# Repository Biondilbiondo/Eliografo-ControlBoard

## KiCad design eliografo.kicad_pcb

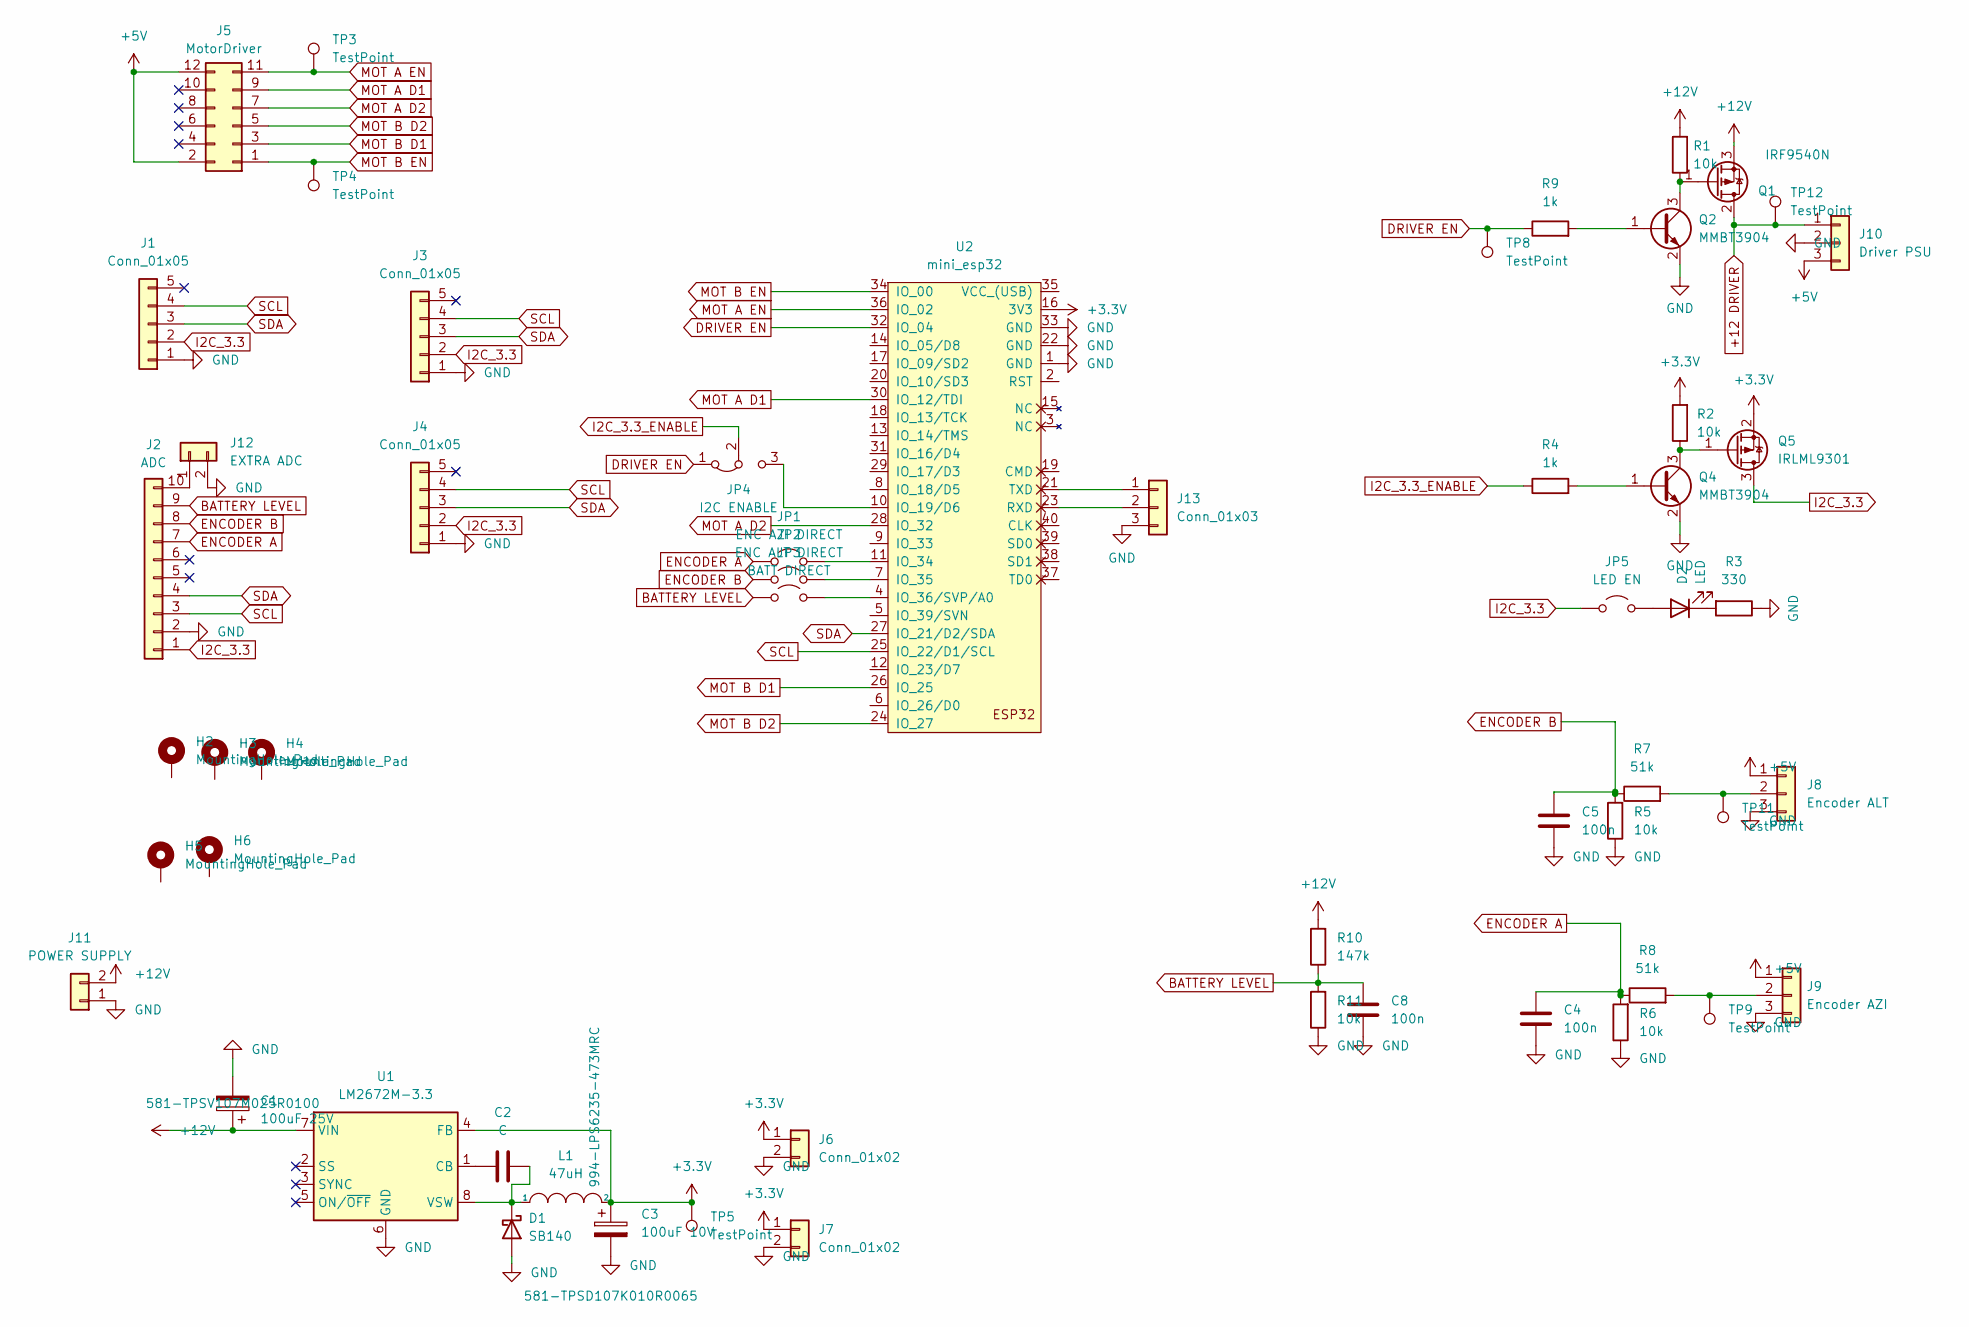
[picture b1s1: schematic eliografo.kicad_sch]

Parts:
C1: 100uF 25V; CP_EIA-7361-38_AVX-V_HandSolder
C2: C; C_0805_2012Metric_Pad1.18x1.45mm_HandSolder
C3: 100uF 10V; CP_EIA-7343-15_Kemet-W_HandSolder
C4, C5, C8: 100n; C_0805_2012Metric_Pad1.18x1.45mm_HandSolder
D1: SB140; D_SMA
D2: LED; LED_D3.0mm
H2, H3, H4, H5, H6: MountingHole_Pad; MountingHole_3.2mm_M3_Pad
J1, J3, J4: Conn_01x05; PinSocket_1x05_P2.54mm_Vertical
J2: ADC; PinSocket_1x10_P2.54mm_Vertical
J5: MotorDriver; IDC-Header_2x06_P2.54mm_Vertical
J6, J7: Conn_01x02; PinHeader_2x01_P2.54mm_Vertical
J8: Encoder ALT; TerminalBlock_Phoenix_MKDS-1,5-3-5.08_1x03_P5.08mm_Horizont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
J9: Encoder AZI; TerminalBlock_Phoenix_MKDS-1,5-3-5.08_1x03_P5.08mm_Horizont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
J10: Driver PSU; TerminalBlock_Phoenix_MKDS-1,5-3-5.08_1x03_P5.08mm_Horizont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
J11: POWER SUPPLY; TerminalBlock_Phoenix_MKDS-1,5-2-5.08_1x02_P5.08mm_Horizont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
J12: EXTRA ADC; PinHeader_1x02_P2.54mm_Vertical
J13: Conn_01x03; PinHeader_1x03_P2.54mm_Vertical
JP1: ENC AZI DIRECT; PinHeader_1x02_P2.54mm_Vertical
JP2: ENC ALT DIRECT; PinHeader_1x02_P2.54mm_Vertical
JP3: BATT DIRECT; PinHeader_1x02_P2.54mm_Vertical
JP4: I2C ENABLE; PinHeader_1x03_P2.54mm_Vertical
JP5: LED EN; PinHeader_1x02_P2.54mm_Vertical
L1: 47uH; L_Coilcraft_XAL6060-XXX
Q1: IRF9540N; TO-252-3_TabPin2
Q2, Q4: MMBT3904; SOT-23
Q5: IRLML9301; SOT-23
R1, R2, R5, R6, R11: 10k; R_0805_2012Metric_Pad1.20x1.40mm_HandSolder
R3: 330; R_0805_2012Metric_Pad1.20x1.40mm_HandSolder
R4, R9: 1k; R_0805_2012Metric_Pad1.20x1.40mm_HandSolder
R7, R8: 51k; R_0805_2012Metric_Pad1.20x1.40mm_HandSolder
R10: 147k; R_0805_2012Metric_Pad1.20x1.40mm_HandSolder
TP3, TP4, TP5, TP8, TP9, TP11, TP12: TestPoint; TestPoint_THTPad_D2.0mm_Drill1.0mm
U1: LM2672M-3.3; SOIC-8_3.9x4.9mm_P1.27mm
U2: mini_esp32; ESP32_mini

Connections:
+3.3V: C3.1, J6.1, J7.1, L1.2, Q5.2 (S), R2.2, TP5.1, U1.4 (FB), U2.16 (3V3)
+5V: J5.2, J5.12, J8.1, J9.1, J10.3
+12 DRIVER: J10.1, Q1.2 (D), TP12.1
+12V: C1.1, J11.2, Q1.3 (S), R1.2, R10.2, U1.7 (VIN)
BATTERY LEVEL: C8.1, J2.9, JP3.1 (A), R10.1, R11.2
DRIVER EN: JP4.1 (A), R9.1, TP8.1, U2.32 (IO_04)
ENCODER A: C4.1, J2.7, JP1.1 (A), R6.2, R8.1
ENCODER B: C5.1, J2.8, JP2.1 (A), R5.2, R7.1
GND: C1.2, C3.2, C4.2, C5.2, C8.2, D1.2 (A), J1.1, J2.2, J3.1, J4.1, J6.2, J7.2, J8.3, J9.3, J10.2, J11.1, J12.2, J13.3, Q2.2 (E), Q4.2 (E), R3.1, R5.1, R6.1, R11.1, U1.6 (GND), U2.1 (GND), U2.22 (GND), U2.33 (GND)
I2C_3.3: J1.2, J2.1, J3.2, J4.2, JP5.1 (A), Q5.3 (D)
I2C_3.3_ENABLE: JP4.2 (C), R4.1
MOT A D1: J5.9, U2.30 (IO_12/TDI)
MOT A D2: J5.7, U2.28 (IO_32)
MOT A EN: J5.11, TP3.1, U2.36 (IO_02)
MOT B D1: J5.3, U2.26 (IO_25)
MOT B D2: J5.5, U2.24 (IO_27)
MOT B EN: J5.1, TP4.1, U2.34 (IO_00)
unnamed: C2.2, D1.1 (K), L1.1, U1.8 (VSW)
unnamed: D2.2 (A), JP5.2 (B)
unnamed: D2.1 (K), R3.2
unnamed: J8.2, R7.2, TP11.1
unnamed: J9.2, R8.2, TP9.1
unnamed: J2.10, J12.1
unnamed: J13.1, U2.21 (TXD)
unnamed: J13.2, U2.23 (RXD)
unnamed: JP1.2 (B), U2.11 (IO_34)
unnamed: JP2.2 (B), U2.7 (IO_35)
unnamed: JP3.2 (B), U2.4 (IO_36/SVP/A0)
unnamed: JP4.3 (B), U2.10 (IO_19/D6)
unnamed: Q1.1 (G), Q2.3 (C), R1.1
unnamed: Q2.1 (B), R9.2
unnamed: Q4.1 (B), R4.2
unnamed: Q4.3 (C), Q5.1 (G), R2.1
unnamed: C2.1, U1.1 (CB)
SCL: J1.4, J2.3, J3.4, J4.4, U2.25 (IO_22/D1/SCL)
SDA: J1.3, J2.4, J3.3, J4.3, U2.27 (IO_21/D2/SDA)

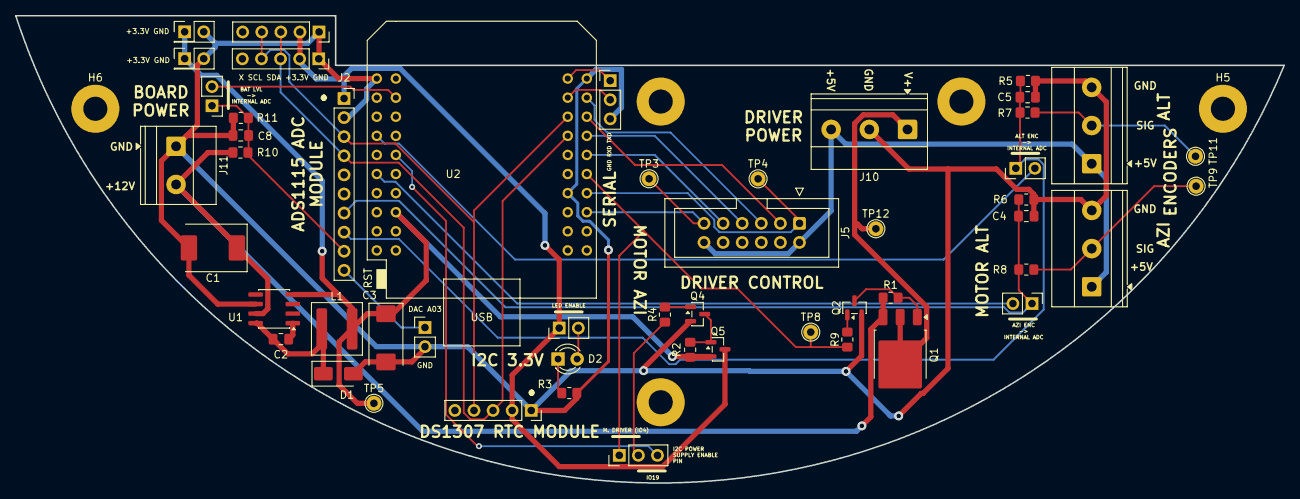
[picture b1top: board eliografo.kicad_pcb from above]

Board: 2 copper layers, 168.7 x 62.1 mm, 56 parts (0 on the bottom side), 36 nets.

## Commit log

2025-11-21 Version 0.1 (used with several modification in Summer 25 installation)
2025-11-21 Modifications added in debug of v0.1
2025-11-21 Added ESP32 mini lib as submodule
2025-11-22 First sketch of version 0.2
2025-11-24 Version 0.2 ready for production
